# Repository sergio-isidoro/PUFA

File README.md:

# 🔥 PUFA

yet to be described!

## Screenshot's

## Photos

## Video

https://github.com/user-attachments/assets/bb75e299-b183-4e6a-995e-6fe85692a9c1

## Github link

[PUFA](https://github.com/manoper93/PUFA)

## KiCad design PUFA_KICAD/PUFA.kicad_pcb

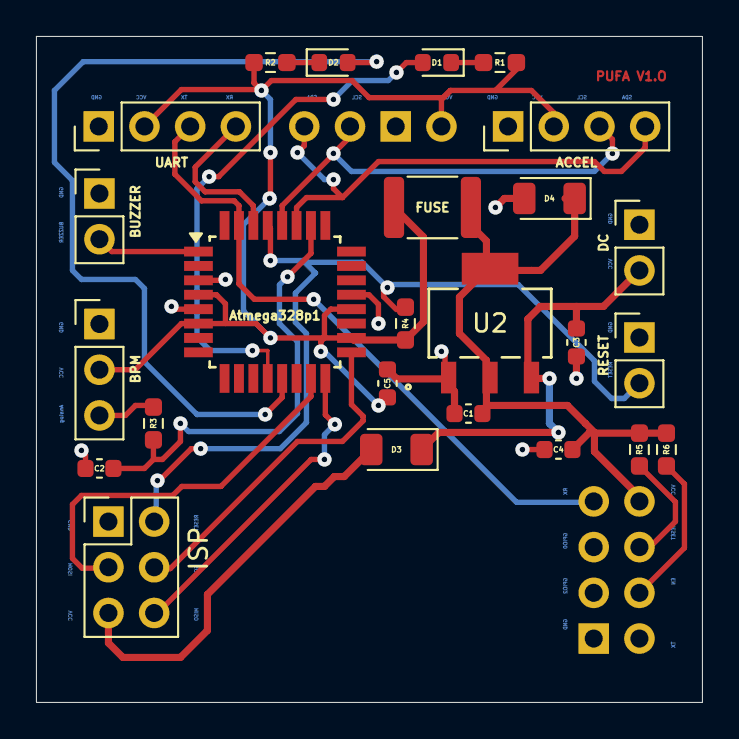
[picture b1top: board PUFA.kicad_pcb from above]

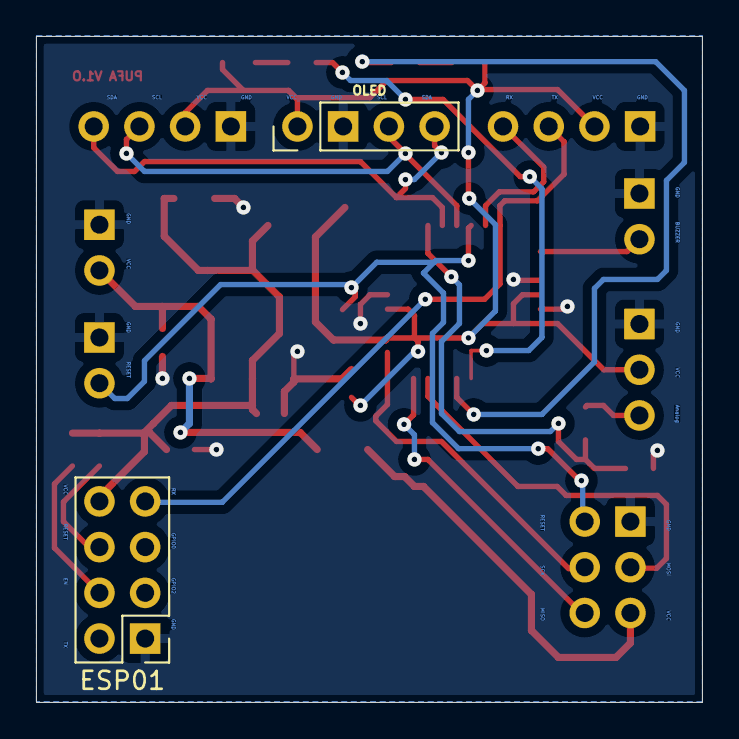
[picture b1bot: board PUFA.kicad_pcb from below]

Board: 2 copper layers, 37.0 x 37.0 mm, 27 parts (2 on the bottom side), 15 nets.

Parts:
ACCEL: PinHeader_1x04_P2.54mm_Vertical
Atmega328p1: ATmega328P-A; TQFP-32_7x7mm_P0.8mm
BPM: PinHeader_1x03_P2.54mm_Vertical
BUZZER: PinHeader_1x02_P2.54mm_Vertical
C1, C2, C3, C4, C5: C_0603_1608Metric
D1, D2: LED_0603_1608Metric
D3, D4: D_1206_3216Metric
DC: PinHeader_1x02_P2.54mm_Vertical
ESP01: PinHeader_2x04_P2.54mm_Vertical
FUSE: Fuse_1812_4532Metric
ISP: PinHeader_2x03_P2.54mm_Vertical
OLED: PinHeader_1x04_P2.54mm_Vertical
R1, R2, R3, R4, R5, R6: R_0603_1608Metric_Pad0.98x0.95mm_HandSolder
RESET: PinHeader_1x02_P2.54mm_Vertical
U2: AP2114HA_3.3V; SOT-223_DIO
UART: PinHeader_1x04_P2.54mm_Vertical

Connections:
/ADC3: Atmega328p1.26 (PC3), BPM.3, C2.1, R3.1, R3.2
/MISO: Atmega328p1.16 (PB4), ISP.6
/MOSI: Atmega328p1.15 (PB3), ISP.3
/PB0: Atmega328p1.12 (PB0), D1.2
/PB1: Atmega328p1.13 (PB1), D2.2
/PD3: Atmega328p1.1 (PD3), BUZZER.2
/RESET: Atmega328p1.29 (~RESET/PC6), ISP.2, R4.2, RESET.2
/RX: Atmega328p1.30 (PD0), UART.4
/SCK: Atmega328p1.17 (PB5), ISP.4
/SCL: ACCEL.3, Atmega328p1.28 (PC5), OLED.3
/SDA: ACCEL.4, Atmega328p1.27 (PC4), OLED.4
/TX: Atmega328p1.31 (PD1), ESP01.7, UART.3
GND: ACCEL.1, Atmega328p1.3 (GND), Atmega328p1.5 (GND), Atmega328p1.21 (GND), BPM.1, BUZZER.1, C1.2, C2.2, C3.2, C4.2, C5.2, D4.2, DC.1, ESP01.1, ISP.1, OLED.1, RESET.1, U2.1 (VIN), UART.1
VCC: ACCEL.2, Atmega328p1.4 (VCC), Atmega328p1.6 (VCC), Atmega328p1.18 (AVCC), Atmega328p1.20 (AREF), BPM.2, C1.1, C4.1, C5.1, D4.1, ESP01.8, FUSE.1, FUSE.2, OLED.1, R1.2, R2.1, R4.1, R5.2, R6.1, U2.2 (GND), U2.4 (EPAD), UART.2
Vin: C3.1, D3.1, D3.2, DC.2, ISP.5, U2.3 (VOUT)
